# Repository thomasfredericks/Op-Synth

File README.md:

# Op-Synth

Op-Synth is an open-source modular micro analog synthesizer designed to facilitate the understanding of electronics, audio synthesis, sound theory, and filtering.

Op-Synth is a 100% analog kit that requires assembly. It is easy to build and serves as an excellent introduction to electronics. It teaches the basic principles of sound synthesis through a modular patch bay, just like a traditional modular analog synthesizer. It also features an LED that helps visualize the evolution of the sound signal, serving as a basic introduction to synesthesia.

In addition to generating its own audio signal, the Op-Synth includes an audio input, allowing musicians to manipulate sounds from their cellphone, music player, or electric guitar. Multiple Op-Synths can be chained together to create more complex sonic textures. Despite its small size (3" x 3"), this synthesizer is powerful and affordable.

All circuitry is built as independent modules that are easy to isolate, understand, and hack.

## Videos

* [Op-Synth Introduction](https://vimeo.com/214735193)
* [Op-Synth Basics Tutorial](https://vimeo.com/225257448)
* [Op-Synth : Adding the Optional External Photocell and Diode](https://vimeo.com/225840352)
* [Op-Synth : External Input](https://vimeo.com/209483661)
* [Op-Synth Hacking : External LED](https://vimeo.com/212077716)

## Credits

* Electronics : Thomas O Fredericks
* Graphical design and illustrations : Denis Raby 

## Booklet

[20 page booklet in French](Op-Synth(livret).pdf)

## Technical Specifications

* 1x resistance controlled (either with a potentiometer or light sensitive sensor) triangle oscillator
* 1x pitch modulation of the previous oscillator
* 1x resistance controlled (either with a potentiometer or light sensitive sensor) low frequency triangle oscillator
* 1x light and resistance controlled filter with feedback control
* 1x PWM (pulse width modulation) module that can also distort and output square waves
* 1x switch that turns on the LED
* 1x LED (the led can be controlled with the switch or another signal)
* 1x stereo output (two independent signals)
* 1x stereo input (two independent signals)
* 5V to 9V battery powered

### Inputs and Outputs of the Patchbay

* in left
* in right
* vco : resistance controlled oscillator
* ~vco : pitch modulation
* lfo : low frequency resistance controlled oscillator
* ~led : led modulation
* pwm (input, modulation, output) : pulse width modulation
* filter in
* filter out
* out left
* out right

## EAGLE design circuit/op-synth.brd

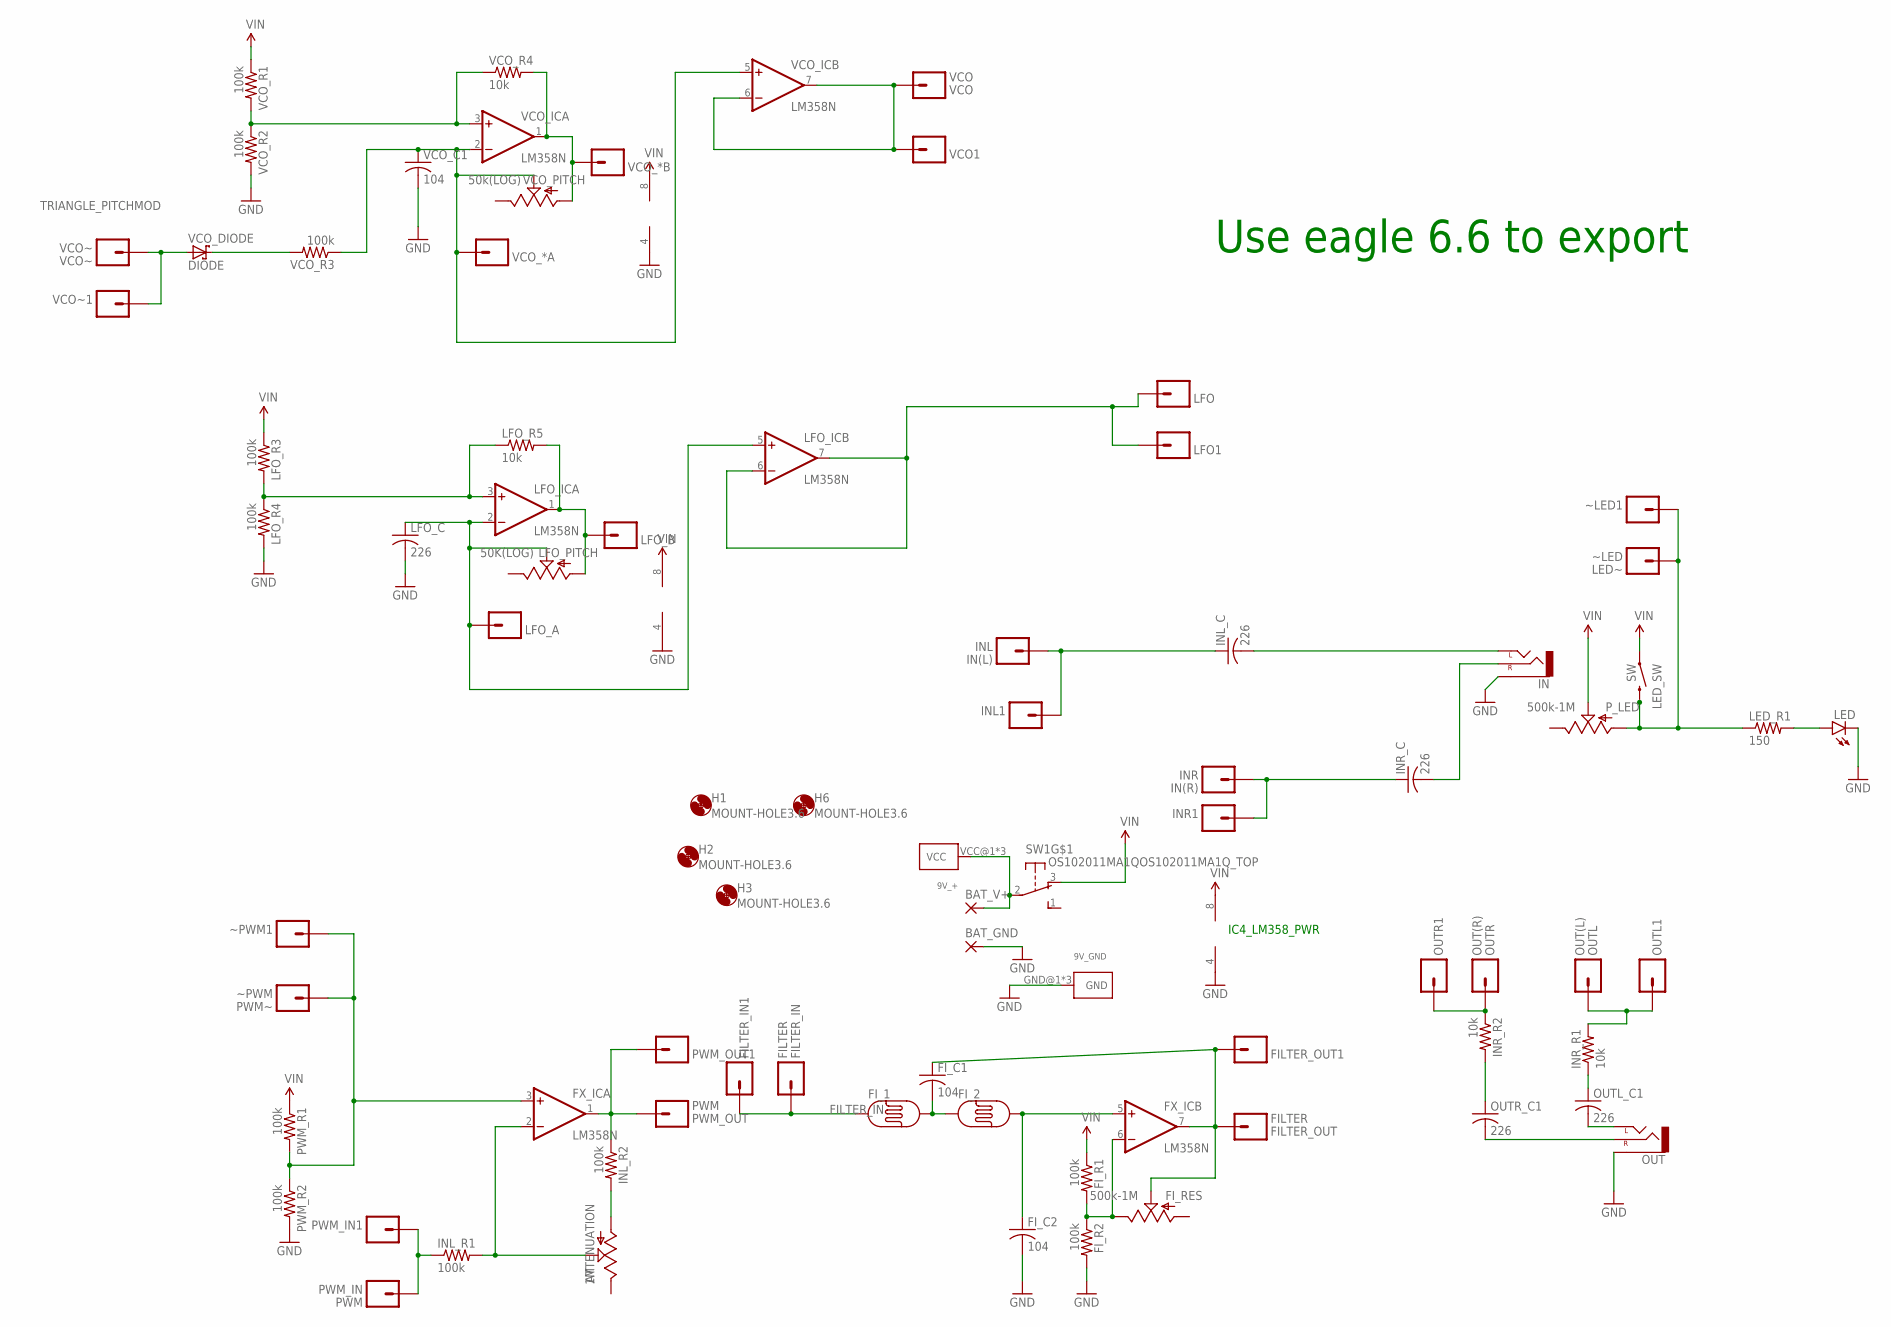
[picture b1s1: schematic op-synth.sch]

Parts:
9V_+: KEYSTONE-637; KEYSTONE_AA_AAA_BATTERY_TERMINAL-637
9V_GND: KEYSTONE-629; KEYSTONE_AA_AAA_BATTERY_TERMINAL-629
ATTENUATION: 1M; TRIM_POT
BAT_GND: 3,81/1,4
BAT_V+: 3,81/1,4
FILTER_IN: FILTER; 1X01_SIDE_NAME
FILTER_IN1: HEADER-1X1; 1X01_SIDE_NAME
FILTER_OUT: FILTER; 1X01_SIDE_NAME
FILTER_OUT1: HEADER-1X1; 1X01_SIDE_NAME
FI_1, FI_2: PHOTOCELLPTH; PHOTOCELL
FI_C1, FI_C2: 104; C050-024X044
FI_R1, FI_R2: 100k; 0204/7
FI_RES: 500k-1M; ALPS_POT
FX_IC: LM358N; DIL08
H1, H2, H3, H6: MOUNT-HOLE3.6; 3,6
IN: AUDIO-JACKPTH; AUDIO-JACK
INL: IN(L); 1X01_SIDE_NAME
INL1: HEADER-1X1; 1X01_SIDE_NAME
INL_C: 226; C050-024X044
INL_R1, INL_R2: 100k; 0204/7
INR: IN(R); 1X01_SIDE_NAME
INR1: HEADER-1X1; 1X01_SIDE_NAME
INR_C: 226; C050-024X044
INR_R1, INR_R2: 10k; 0204/7
LED: LED5MM
LED_R1: 150; 0204/7
LED_SW: SW; TACTILE-PTH-12MM
LFO, LFO1: HEADER-1X1; 1X01_SIDE_NAME
LFO_A: HEADER-1X1; 1X01_SIDE_NAME
LFO_B: HEADER-1X1; 1X01_SIDE_NAME
LFO_C: 226; C050-024X044
LFO_IC: LM358N; DIL08
LFO_PITCH: 50K(LOG); ALPS_POT
LFO_R3, LFO_R4: 100k; 0204/7
LFO_R5: 10k; 0204/7
OUT: AUDIO-JACKPTH; AUDIO-JACK
OUTL: OUT(L); 1X01_SIDE_NAME
OUTL1: HEADER-1X1; 1X01_SIDE_NAME
OUTL_C1: 226; C050-024X044
OUTR: OUT(R); 1X01_SIDE_NAME
OUTR1: HEADER-1X1; 1X01_SIDE_NAME
OUTR_C1: 226; C050-024X044
PWM_IN: PWM; 1X01_SIDE_NAME
PWM_IN1: HEADER-1X1; 1X01_SIDE_NAME
PWM_OUT: PWM; 1X01_SIDE_NAME
PWM_OUT1: HEADER-1X1; 1X01_SIDE_NAME
PWM_R1, PWM_R2: 100k; 0204/7
P_LED: 500k-1M; ALPS_POT
SW1: OS102011MA1QOS102011MA1Q_TOP; OS102011MA1Q
VCO: VCO; 1X01_SIDE_NAME
VCO1: HEADER-1X1; 1X01_SIDE_NAME
VCO_*A: HEADER-1X1; 1X01_SIDE_NAME
VCO_*B: HEADER-1X1; 1X01_SIDE_NAME
VCO_C1: 104; C050-024X044
VCO_DIODE: DIODE; DO41-7
VCO_IC: LM358N; DIL08
VCO_PITCH: 50k(LOG); ALPS_POT
VCO_R1, VCO_R2, VCO_R3: 100k; 0204/7
VCO_R4: 10k; 0204/7
VCO~: VCO~; 1X01_SIDE_NAME
VCO~1: HEADER-1X1; 1X01_SIDE_NAME
~LED: LED~; 1X01_SIDE_NAME
~LED1: HEADER-1X1; 1X01_SIDE_NAME
~PWM: PWM~; 1X01_SIDE_NAME
~PWM1: HEADER-1X1; 1X01_SIDE_NAME

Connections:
FILTER_IN: FILTER_IN.1, FILTER_IN1.1, FI_1.1
FILTER_OUT: FILTER_OUT.1, FILTER_OUT1.1, FI_C1.1, FI_RES.P$2 (S), FX_IC.7 (OUT)
GND: 9V_GND.GND@1, 9V_GND.GND@2, 9V_GND.GND@3, BAT_GND.1, FI_C2.2, FI_R2.2, FX_IC.4 (V-), IN.SLEEVE, LED.K (C), LFO_C.2, LFO_IC.4 (V-), LFO_R4.2, OUT.SLEEVE, PWM_R2.2, VCO_C1.2, VCO_IC.4 (V-), VCO_R2.2
LFO: LFO.1, LFO1.1, LFO_IC.6 (-IN), LFO_IC.7 (OUT)
unnamed: 9V_+.VCC@1, 9V_+.VCC@2, 9V_+.VCC@3, BAT_V+.1, SW1.2
unnamed: VCO_DIODE.C, VCO_R3.2
unnamed: ATTENUATION.3 (A), INL_R2.2
unnamed: VCO_IC.3 (+IN), VCO_R1.2, VCO_R2.1, VCO_R4.1
unnamed: FX_IC.3 (+IN), PWM_R1.2, PWM_R2.1, ~PWM.1, ~PWM1.1
unnamed: LED.A, LED_R1.2
unnamed: FI_2.2, FI_C2.1, FX_IC.5 (+IN)
unnamed: FI_1.2, FI_2.1, FI_C1.2
unnamed: INR_R2.1, OUTR.1, OUTR1.1
unnamed: VCO_*B.1, VCO_IC.1 (OUT), VCO_PITCH.P$3 (A), VCO_R4.2
unnamed: OUT.TIP (LEFT), OUTL_C1.2
unnamed: INL_R1.1, PWM_IN.1, PWM_IN1.1
unnamed: LED_R1.1, LED_SW.3 (2), P_LED.P$3 (A), ~LED.1, ~LED1.1
unnamed: INR.1, INR1.1, INR_C.1
unnamed: IN.RING (RIGHT), INR_C.2
unnamed: FI_R1.2, FI_R2.1, FI_RES.P$1 (E), FX_IC.6 (-IN)
unnamed: LFO_IC.3 (+IN), LFO_R3.2, LFO_R4.1, LFO_R5.1
unnamed: VCO_*A.1, VCO_C1.1, VCO_IC.2 (-IN), VCO_IC.5 (+IN), VCO_PITCH.P$2 (S), VCO_R3.1
unnamed: INL.1, INL1.1, INL_C.1
unnamed: IN.TIP (LEFT), INL_C.2
unnamed: LFO_B.1, LFO_IC.1 (OUT), LFO_PITCH.P$3 (A), LFO_R5.2
unnamed: LFO_A.1, LFO_C.1, LFO_IC.2 (-IN), LFO_IC.5 (+IN), LFO_PITCH.P$2 (S)
unnamed: VCO.1, VCO1.1, VCO_IC.6 (-IN), VCO_IC.7 (OUT)
unnamed: OUT.RING (RIGHT), OUTR_C1.2
unnamed: ATTENUATION.1 (S), FX_IC.2 (-IN), INL_R1.2
unnamed: FX_IC.1 (OUT), INL_R2.1, PWM_OUT.1, PWM_OUT1.1
unnamed: INR_R2.2, OUTR_C1.1
unnamed: INR_R1.2, OUTL.1, OUTL1.1
unnamed: INR_R1.1, OUTL_C1.1
TRIANGLE_PITCHMOD: VCO_DIODE.A, VCO~.1, VCO~1.1
VIN: FI_R1.1, FX_IC.8 (V+), LED_SW.1, LFO_IC.8 (V+), LFO_R3.1, PWM_R1.1, P_LED.P$2 (S), SW1.3 (O), VCO_IC.8 (V+), VCO_R1.1

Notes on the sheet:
IC4_LM358_PWR
Use eagle 6.6 to export

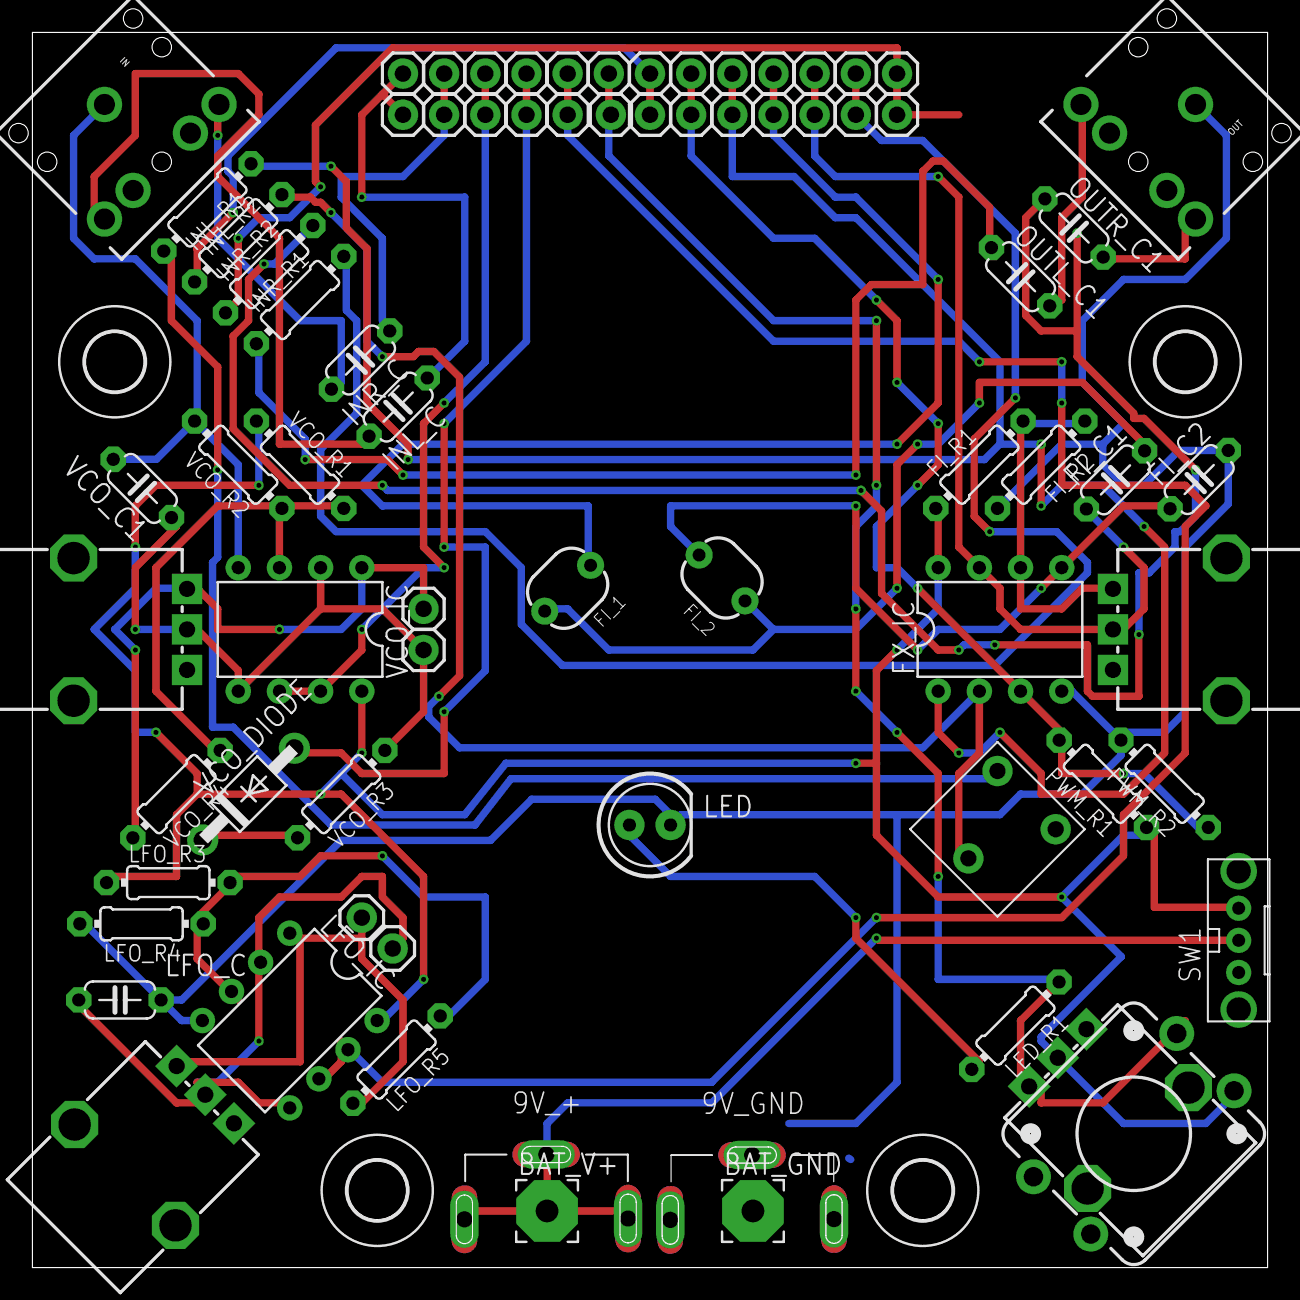
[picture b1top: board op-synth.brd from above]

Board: 2 copper layers, 76.1 x 76.1 mm, 78 parts (0 on the bottom side), 35 nets.

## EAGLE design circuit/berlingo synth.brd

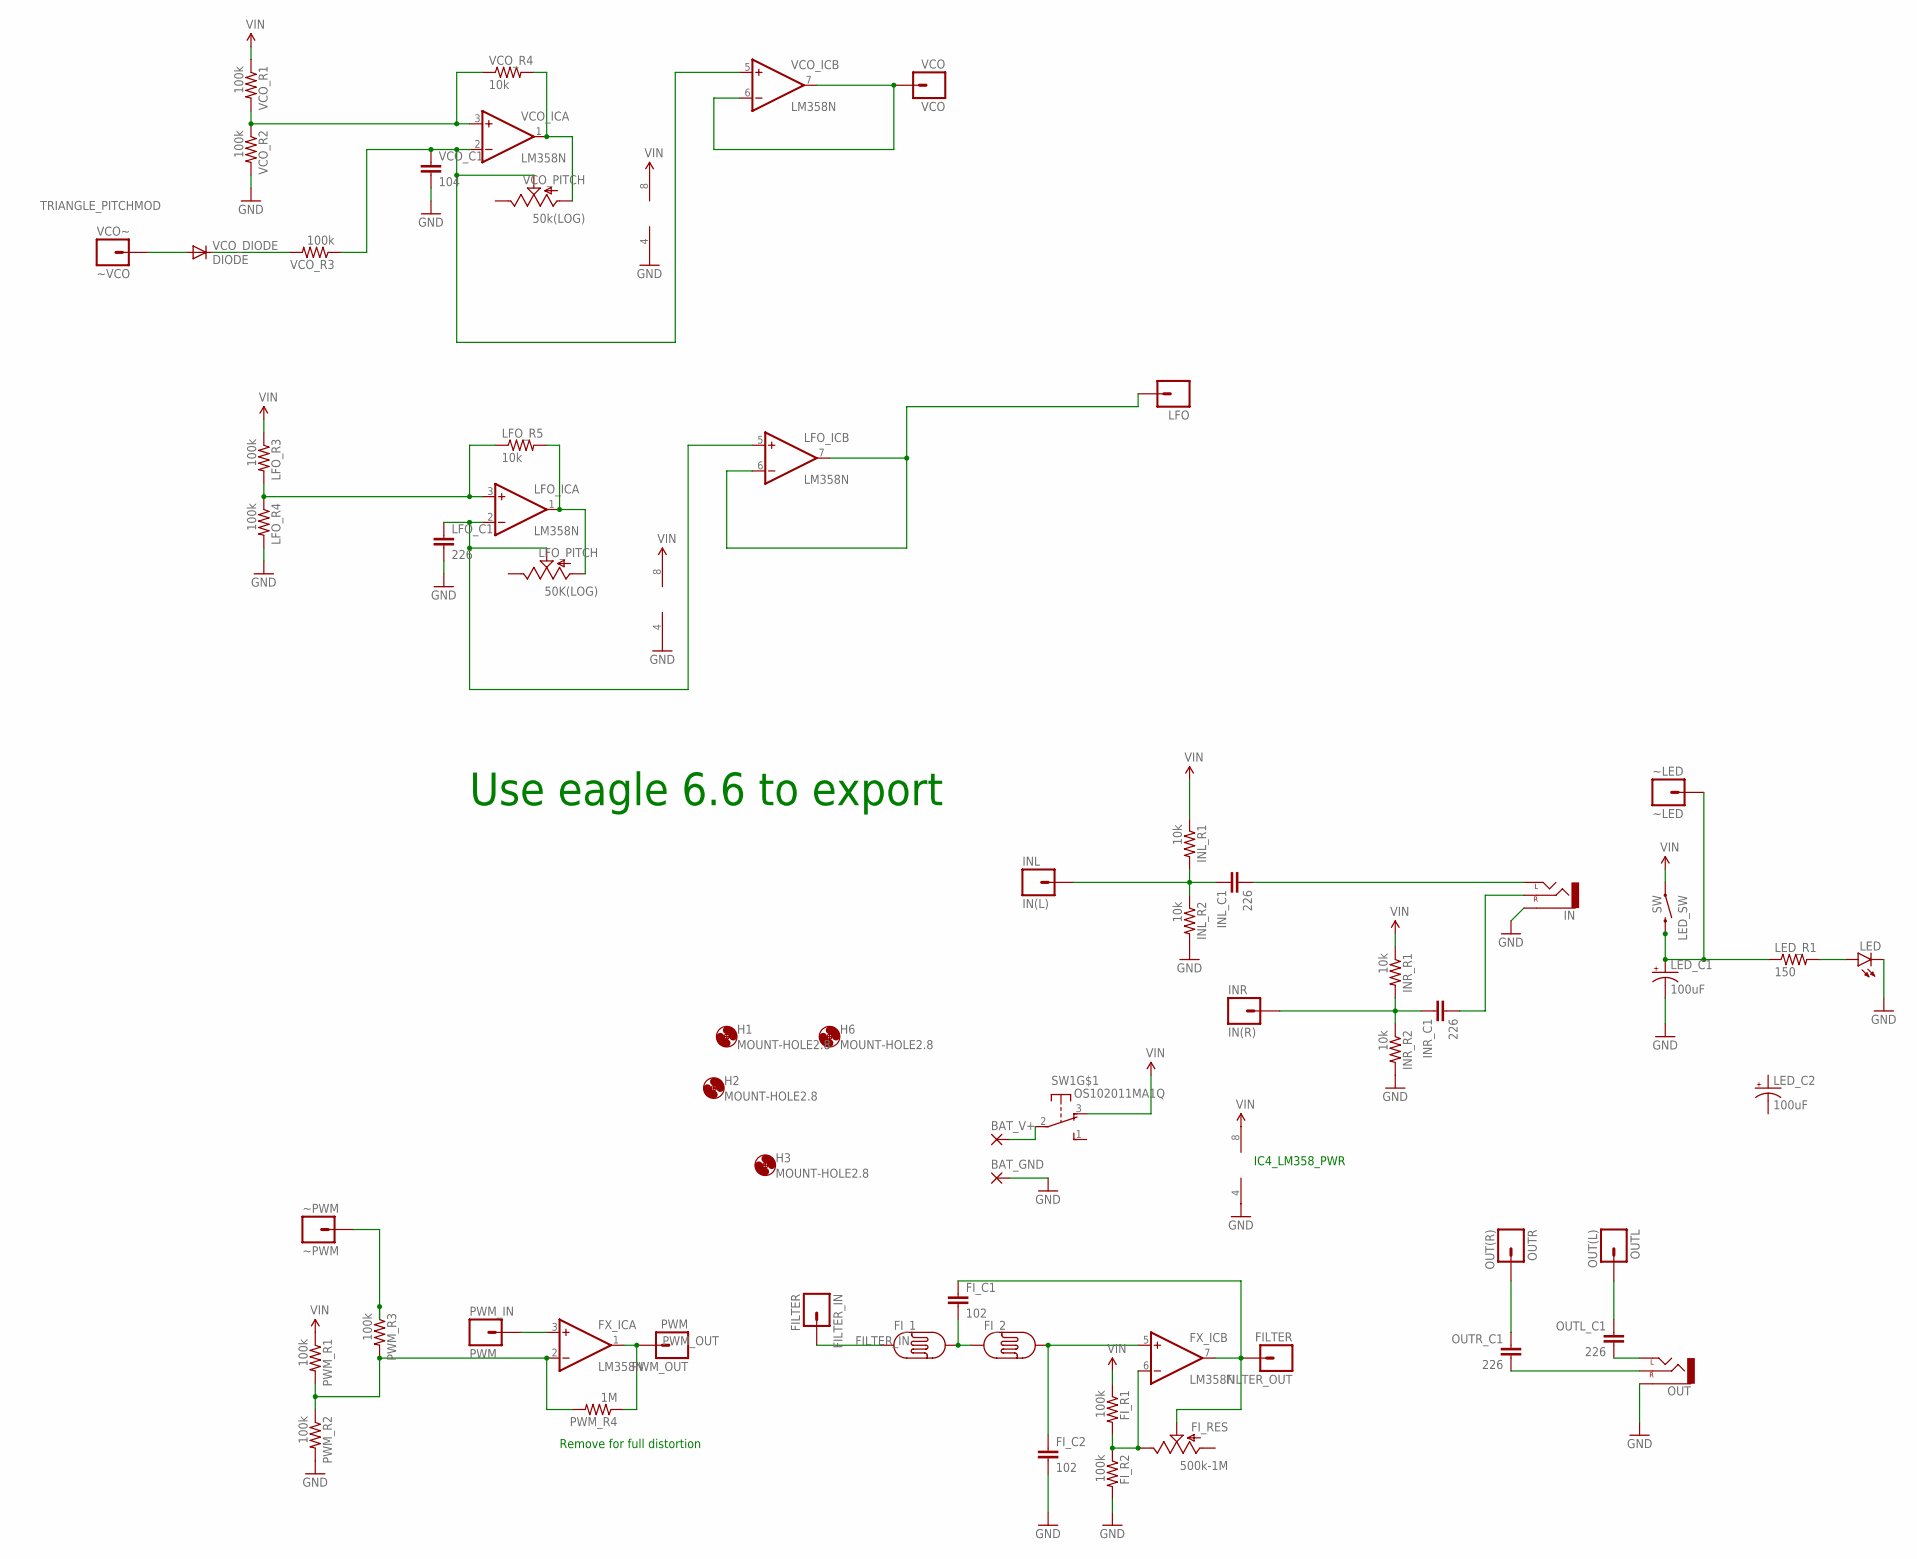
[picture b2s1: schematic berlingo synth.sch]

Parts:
BAT_GND: 3,81/1,4
BAT_V+: 3,81/1,4
FILTER_IN: FILTER; 1X01_SIDE_NAME
FILTER_OUT: FILTER; 1X01_SIDE_NAME
FI_1, FI_2: PHOTOCELLPTH; PHOTOCELL
FI_C1, FI_C2: 102; CAP-PTH-SMALLEZ
FI_R1, FI_R2: 100k; 0207/10
FI_RES: 500k-1M; ALPS_POT
FX_IC: LM358N; DIL08
H1, H2, H3, H6: MOUNT-HOLE2.8; 2,8
IN: AUDIO-JACKPTH; AUDIO-JACK
INL: IN(L); 1X01_SIDE_NAME
INL_C1: 226; CAP-PTH-SMALLEZ
INL_R1, INL_R2: 10k; 0207/10
INR: IN(R); 1X01_SIDE_NAME
INR_C1: 226; CAP-PTH-SMALLEZ
INR_R1, INR_R2: 10k; 0207/10
LED: LED5MM
LED_C1: 100uF; E2-4
LED_C2: 100uF; E2,5-6
LED_R1: 150; 0207/10
LED_SW: SW; TACTILE-PTH-12MM
LFO: HEADER-1X1; 1X01_SIDE_NAME
LFO_C1: 226; CAP-PTH-SMALLEZ
LFO_IC: LM358N; DIL08
LFO_PITCH: 50K(LOG); ALPS_POT
LFO_R3, LFO_R4: 100k; 0207/10
LFO_R5: 10k; 0207/10
OUT: AUDIO-JACKPTH; AUDIO-JACK
OUTL: OUT(L); 1X01_SIDE_NAME
OUTL_C1: 226; CAP-PTH-SMALLEZ
OUTR: OUT(R); 1X01_SIDE_NAME
OUTR_C1: 226; CAP-PTH-SMALLEZ
PWM_IN: PWM; 1X01_SIDE_NAME
PWM_OUT: PWM; 1X01_SIDE_NAME
PWM_R1, PWM_R2, PWM_R3: 100k; 0207/10
PWM_R4: 1M; 0207/10
SW1: OS102011MA1Q
VCO: VCO; 1X01_SIDE_NAME
VCO_C1: 104; CAP-PTH-SMALLEZ
VCO_DIODE: DIODE; DO41-10
VCO_IC: LM358N; DIL08
VCO_PITCH: 50k(LOG); ALPS_POT
VCO_R1, VCO_R2, VCO_R3: 100k; 0207/10
VCO_R4: 10k; 0207/10
VCO~: ~VCO; 1X01_SIDE_NAME
~LED: ~LED; 1X01_SIDE_NAME
~PWM: ~PWM; 1X01_SIDE_NAME

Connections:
FILTER_IN: FILTER_IN.1, FI_1.1
FILTER_OUT: FILTER_OUT.1, FI_C1.1, FI_RES.P$2 (S), FX_IC.7 (OUT)
GND: BAT_GND.1, FI_C2.2, FI_R2.2, FX_IC.4 (V-), IN.SLEEVE, INL_R2.2, INR_R2.2, LED.K (C), LED_C1.-, LFO_C1.2, LFO_IC.4 (V-), LFO_R4.2, OUT.SLEEVE, PWM_R2.2, VCO_C1.2, VCO_IC.4 (V-), VCO_R2.2
LFO: LFO.1, LFO_IC.6 (-IN), LFO_IC.7 (OUT)
MOD_IN: FX_IC.3 (+IN), PWM_IN.1
unnamed: BAT_V+.1, SW1.2
unnamed: VCO_DIODE.C, VCO_R3.2
unnamed: FX_IC.2 (-IN), PWM_R1.2, PWM_R2.1, PWM_R3.2, PWM_R4.2
unnamed: VCO_IC.3 (+IN), VCO_R1.2, VCO_R2.1, VCO_R4.1
unnamed: PWM_R3.1, ~PWM.1
unnamed: LED.A, LED_R1.2
unnamed: FI_2.2, FI_C2.1, FX_IC.5 (+IN)
unnamed: FI_1.2, FI_2.1, FI_C1.2
unnamed: OUTR.1, OUTR_C1.1
unnamed: VCO_IC.1 (OUT), VCO_PITCH.P$3 (A), VCO_R4.2
unnamed: OUT.TIP (LEFT), OUTL_C1.2
unnamed: OUTL.1, OUTL_C1.1
unnamed: LED_C1.+, LED_R1.1, LED_SW.3 (2), ~LED.1
unnamed: INR.1, INR_C1.1, INR_R1.2, INR_R2.1
unnamed: IN.RING (RIGHT), INR_C1.2
unnamed: FI_R1.2, FI_R2.1, FI_RES.P$1 (E), FX_IC.6 (-IN)
unnamed: LFO_IC.3 (+IN), LFO_R3.2, LFO_R4.1, LFO_R5.1
unnamed: VCO_C1.1, VCO_IC.2 (-IN), VCO_IC.5 (+IN), VCO_PITCH.P$2 (S), VCO_R3.1
unnamed: INL.1, INL_C1.1, INL_R1.2, INL_R2.1
unnamed: IN.TIP (LEFT), INL_C1.2
unnamed: LFO_IC.1 (OUT), LFO_PITCH.P$3 (A), LFO_R5.2
unnamed: LFO_C1.1, LFO_IC.2 (-IN), LFO_IC.5 (+IN), LFO_PITCH.P$2 (S)
unnamed: VCO.1, VCO_IC.6 (-IN), VCO_IC.7 (OUT)
unnamed: OUT.RING (RIGHT), OUTR_C1.2
PWM_OUT: FX_IC.1 (OUT), PWM_OUT.1, PWM_R4.1
TRIANGLE_PITCHMOD: VCO_DIODE.A, VCO~.1
VIN: FI_R1.1, FX_IC.8 (V+), INL_R1.1, INR_R1.1, LED_SW.1, LFO_IC.8 (V+), LFO_R3.1, PWM_R1.1, SW1.3 (O), VCO_IC.8 (V+), VCO_R1.1

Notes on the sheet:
IC4_LM358_PWR
Remove for full distortion
Use eagle 6.6 to export

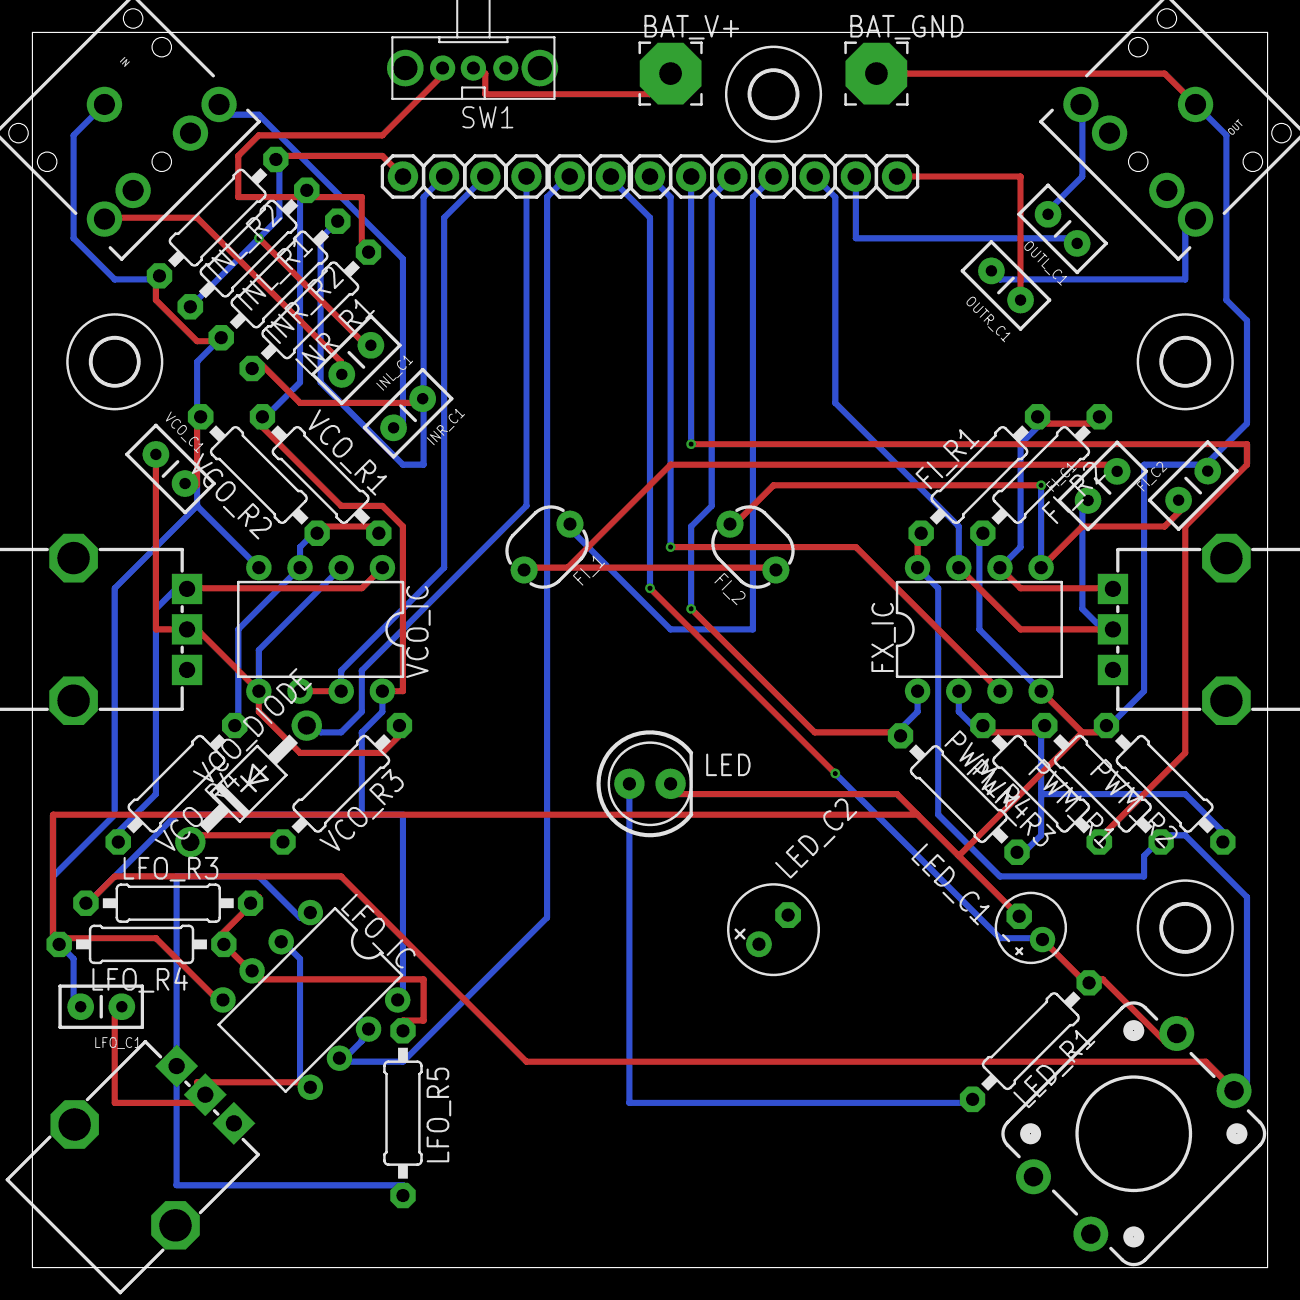
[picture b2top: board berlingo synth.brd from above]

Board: 2 copper layers, 76.2 x 76.2 mm, 61 parts (0 on the bottom side), 32 nets.

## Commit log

2016-03-25 Changed order and added stereo
    Changed order to IN - VCO - VCO~ - LFO - LED - PWM in - PWM~ - PWM out -
    FILTER in - FILTER OUT - OUT - OUT
    Added L and R
2016-04-07 Updated Parts and changed a few part names
2016-04-12 Update BOM, increased trace sizes and added more silkscreen info
2016-05-06 Euh...
2016-09-27 Berlingo Synth 0.5 and 0.6
2016-09-27 Berlingo Synth 0.6
2016-09-27 Removal of previous versions
2016-12-20 Newest version
2016-12-20 Replaced Berlingo Synth name
2017-01-23 Version 0.8
2017-10-25 New version
2018-01-10 version 0.91
2018-01-28 Version 1 and version 2
2018-05-20 Updated pot values
2018-11-06 Updated to latest version
2020-12-12 Added booklet and artwork
2020-12-12 Set theme jekyll-theme-minimal

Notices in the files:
parts and their libraries:
SparkFun-Electromechanical: Licensing: Creative Commons ShareAlike 4.0 International - https://creativecommons.org/licenses/by-sa/4.0
